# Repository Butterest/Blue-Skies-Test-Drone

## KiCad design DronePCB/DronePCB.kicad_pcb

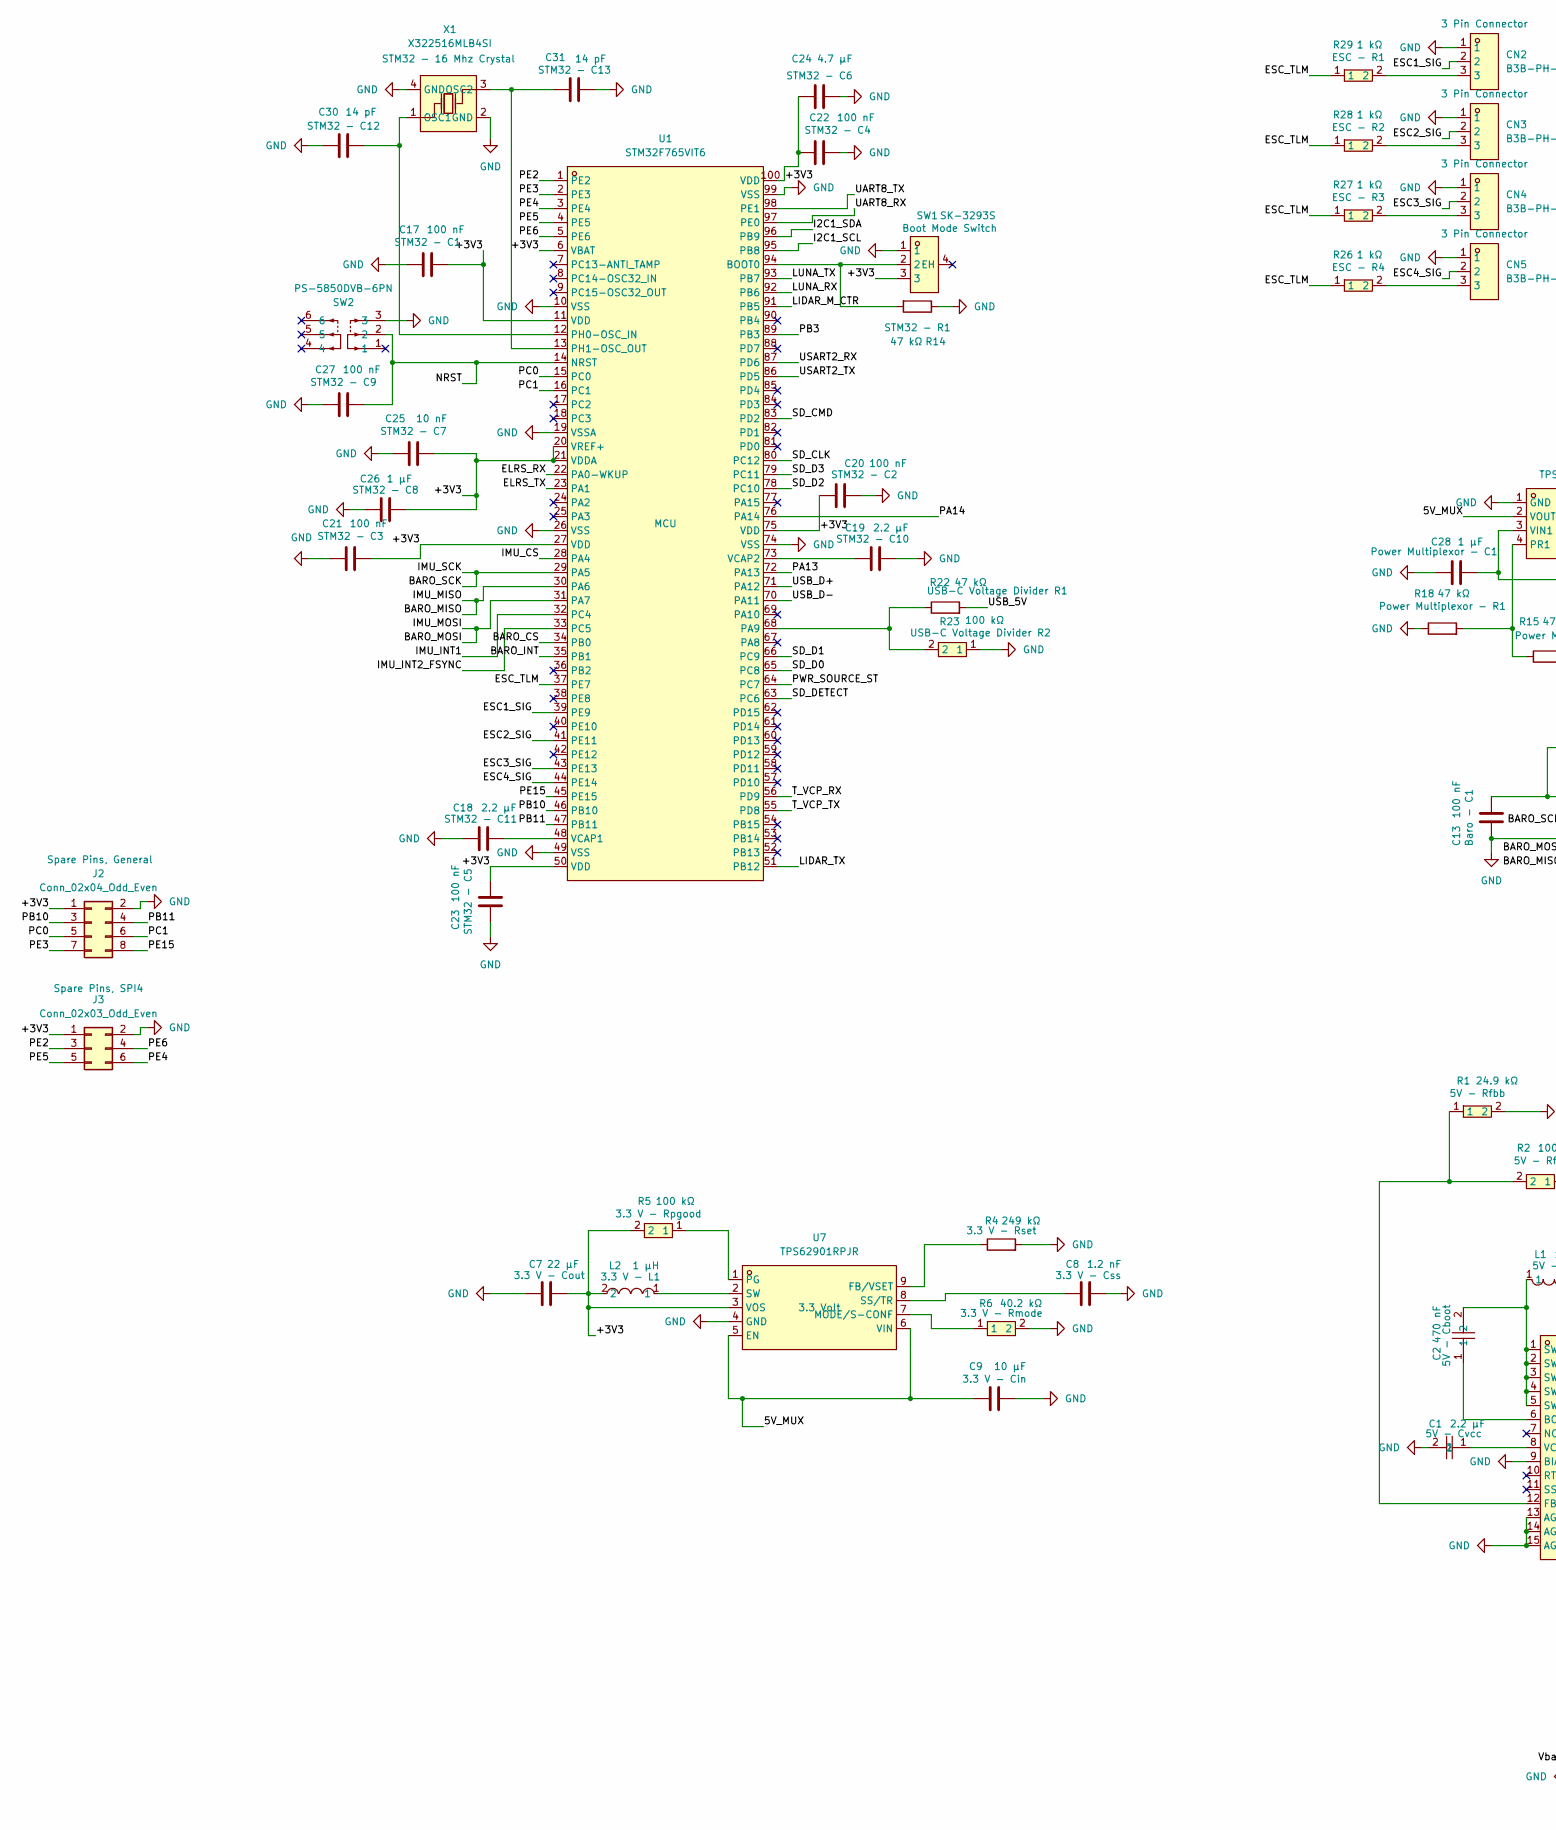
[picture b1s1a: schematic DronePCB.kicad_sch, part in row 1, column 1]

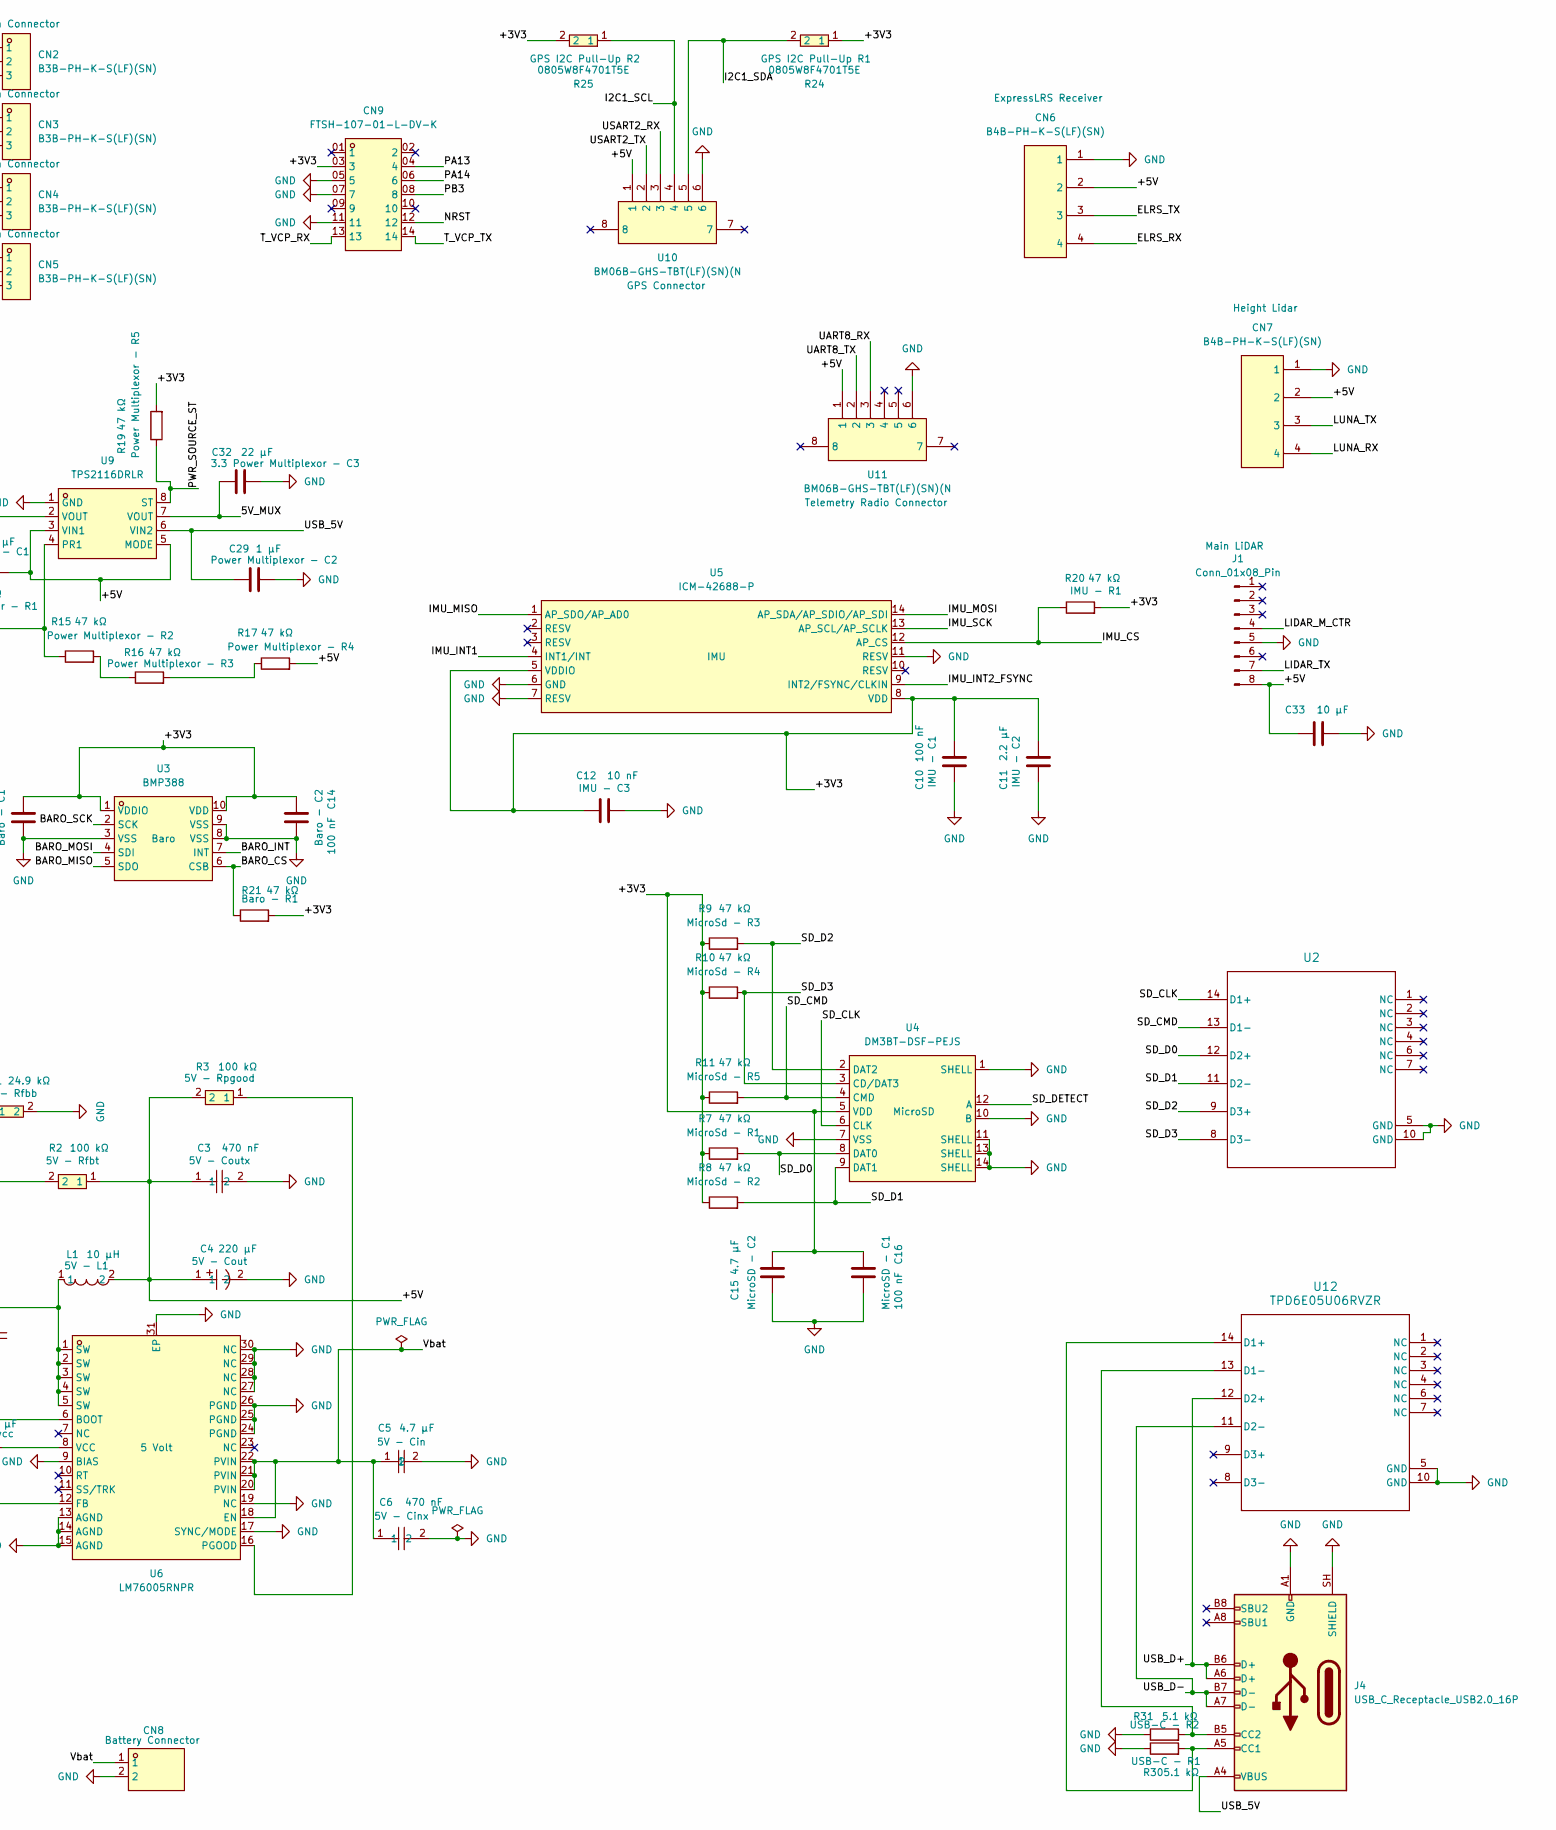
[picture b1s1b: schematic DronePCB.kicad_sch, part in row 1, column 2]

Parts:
C1, C18, C19: 2.2 µF; C_0603_1608Metric; Manufacturer Part # CL10A225KO8NNNC; LCSC Part C23630
C2: 470 nF; C_0402_1005Metric; Manufacturer Part # GRM155R61A474KE15D; LCSC Part C77003
C3: 470 nF; C_0805_2012Metric; Manufacturer Part # EMF212B7474KGHT; LCSC Part C651004
C4: 220 µF; CAP-SMD_L7.3-W4.3; Manufacturer Part # 593D227X0010E2TE3; LCSC Part C1952898
C5, C15, C24: 4.7 µF; C_1206_3216Metric; Manufacturer Part # GRM31CR71H475KA12L; LCSC Part C77096
C6: 470 nF; C_0805_2012Metric; Manufacturer Part # CGA4J3X7R1H474K125AB; LCSC Part C3899838
C7, C32: 22 µF; C_0805_2012Metric; Manufacturer Part # MSASE21GBB5226MTNA01; LCSC Part C140602
C8: 1.2 nF; C_0603_1608Metric; Manufacturer Part # GRM1885C1H122JA01D; LCSC Part C97876
C9, C33: 10 µF; C_0805_2012Metric; Manufacturer Part # MSASE21GAB5106KTNA01; LCSC Part C6684487
C10, C13, C14, C16, C17, C20, C21, C22, C23, C27: 100 nF; C_0402_1005Metric; MPN CL05B104KO5NNNC; LCSC Part C1525
C11: 2.2 µF; C_0805_2012Metric; MPN CL05B104KO5NNNC; LCSC Part C125847
C12, C25: 10 nF; C_0402_1005Metric; MPN CL05B104KO5NNNC; LCSC Part C1524
C26, C28, C29: 1 µF; C_0603_1608Metric; LCSC Part C5199872
C30, C31: 14 pF; C_0402_1005Metric; MPN 0402CG140J500NT; LCSC Part C3037644
CN2, CN3, CN4, CN5: B3B-PH-K-S(LF)(SN); JST_PH_B3B-PH-K_1x03_P2.00mm_Vertical; LCSC Part C131339
CN6, CN7: B4B-PH-K-S(LF)(SN); JST_PH_B4B-PH-K_1x04_P2.00mm_Vertical; LCSC Part C131334
CN8: B2P-VH (LF)(SN); CONN-TH_B2P-VH-LF-SN; MPN B2P-VH (LF)(SN); LCSC Part C160315
CN9: FTSH-107-01-L-DV-K; HDR-SMD_14P-P1.27_FTSH-107-01-L-DV-K; LCSC Part C5307809
J1: Conn_01x08_Pin; JST_PH_B8B-PH-K_1x08_P2.00mm_Vertical; LCSC Part C594302
J2: Conn_02x04_Odd_Even; PinHeader_2x04_P2.54mm_Vertical
J3: Conn_02x03_Odd_Even; PinHeader_2x03_P2.54mm_Vertical
J4: USB_C_Receptacle_USB2.0_16P; USB_C_Receptacle_HRO_TYPE-C-31-M-12; LCSC Part C165948
L1: 10 µH; IND-SMD_L10.2-W10.2-LS10.8; Manufacturer Part # IHLP4040DZER100M01; LCSC Part C845065
L2: 1 µH; L0806; Manufacturer Part # DFE201610E-1R0M=P2; LCSC Part C161082
R1: 24.9 kΩ; R_0603_1608Metric; Manufacturer Part # RC0603FR-0724K9L; LCSC Part C137761
R2, R5, R23: 100 kΩ; R_0402_1005Metric; Manufacturer Part # CRCW0402100KFKED; LCSC Part C481918
R3: 100 kΩ; R_0603_1608Metric; Manufacturer Part # CRCW0603100KFKEA; LCSC Part C844916
R4: 249 kΩ; R_0402_1005Metric; Manufacturer Part Number CRCW0402249KFKEDC; LCSC Part C3009708
R6: 40.2 kΩ; R_0402_1005Metric; Manufacturer Part # CRCW040240K2FKED; LCSC Part C844507
R7, R8, R9, R10, R11, R14, R15, R16, R17, R18, R19, R20, R21, R22: 47 kΩ; R_0805_2012Metric; LCSC Part C17713
R24, R25: 0805W8F4701T5E; R_0805_2012Metric; LCSC Part C17673
R26, R27, R28, R29: 1 kΩ; R_1206_3216Metric; MPN 1206W4J0102T5E; LCSC Part C1469
R30, R31: 5.1 kΩ; R_0805_2012Metric; MPN RESI PTFR0805B5K10P9; LCSC Part C2692693
SW1: SK-3293S; SW-SMD_SK-3293S; LCSC Part C466006
SW2: PS-5850DVB-6PN; SW-TH_6P-L5.8-W5.8-P2.00-LS4.5-BL_1; LCSC Part C5362623
U1: STM32F765VIT6; LQFP-100_L14.0-W14.0-P0.50-LS16.0-BL; LCSC Part C710319
U2, U12: TPD6E05U06RVZR; RVZ0014A; LCSC Part C962978
U3: BMP388; LGA-10_L2.0-W2.0-P0.50-BL; LCSC Part C779278
U4: DM3BT-DSF-PEJS; SIM-SMD_DM3BT-DSF-PEJS; LCSC Part C597972
U5: ICM-42688-P; LGA-14_L3.0-W2.5-P0.50-TL; LCSC Part C1850418
U6: LM76005RNPR; WQFN-30_L6.0-W4.0-P0.50-TL-EP_LM76005RNPR; LCSC Part C2866241
U7: TPS62901RPJR; VQFN-HR-9_L2.0-W1.5-P0.50-BL_TI_RPJ; LCSC Part C2864847
U9: TPS2116DRLR; SOT-583-8_L2.1-W1.6-P0.50-LS1.6-BL; LCSC Part C3235557
U10, U11: BM06B-GHS-TBT(LF)(SN)(N; CONN-SMD_6P-P1.25_BM06B-GHS-TBT-LF-SN-N; LCSC Part C189892
X1: X322516MLB4SI; CRYSTAL-SMD_4P-L3.2-W2.5-BL; LCSC Part C13738

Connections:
/5V_MUX: C9.1, C32.2, U7.5 (EN), U7.6 (VIN), U9.2 (VOUT), U9.7 (VOUT)
/+3V3: C7.1, C10.2, C11.2, C12.1, C13.2, C14.1, C15.2, C16.1, C17.2, C20.1, C21.2, C22.1, C23.2, C24.1, C25.2, C26.2, CN9.03 (3), J2.1, J3.1, L2.2, R5.2, R7.1, R8.1, R9.1, R10.1, R11.1, R19.2, R20.2, R21.2, R24.1, R25.2, SW1.3, U1.6 (VBAT), U1.11 (VDD), U1.20 (VREF+), U1.21 (VDDA), U1.27 (VDD), U1.50 (VDD), U1.75 (VDD), U1.100 (VDD), U3.1 (VDDIO), U3.10 (VDD), U4.5 (VDD), U5.5 (VDDIO), U5.8 (VDD), U7.3 (VOS)
/+5V: C3.1, C4.1, C28.2, C33.1, CN6.2, CN7.2, J1.8, L1.2, R2.1, R3.2, R17.2, U9.3 (VIN1), U9.5 (MODE), U10.1, U11.1
/BARO_CS: R21.1, U1.34 (PB0), U3.6 (CSB)
/BARO_INT: U1.35 (PB1), U3.7 (INT)
/BARO_MISO: U1.30 (PA6), U3.5 (SDO), U5.1 (AP_SDO/AP_AD0)
/BARO_MOSI: U1.31 (PA7), U3.4 (SDI), U5.14 (AP_SDA/AP_SDIO/AP_SDI)
/BARO_SCK: U1.29 (PA5), U3.2 (SCK), U5.13 (AP_SCL/AP_SCLK)
/ELRS_RX: CN6.4, U1.22 (PA0-WKUP)
/ELRS_TX: CN6.3, U1.23 (PA1)
/ESC1_SIG: CN2.2, U1.39 (PE9)
/ESC2_SIG: CN3.2, U1.41 (PE11)
/ESC3_SIG: CN4.2, U1.43 (PE13)
/ESC4_SIG: CN5.2, U1.44 (PE14)
/ESC_TLM: R26.1, R27.1, R28.1, R29.1, U1.37 (PE7)
/I2C1_SCL: R25.1, U1.95 (PB8), U10.4
/I2C1_SDA: R24.2, U1.96 (PB9), U10.5
/IMU_CS: R20.1, U1.28 (PA4), U5.12 (AP_CS)
/IMU_INT1: U1.32 (PC4), U5.4 (INT1/INT)
/IMU_INT2_FSYNC: U1.33 (PC5), U5.9 (INT2/FSYNC/CLKIN)
/LIDAR_M_CTR: J1.4, U1.91 (PB5)
/LIDAR_TX: J1.7, U1.51 (PB12)
/LUNA_RX: CN7.4, U1.92 (PB6)
/LUNA_TX: CN7.3, U1.93 (PB7)
/NRST: C27.2, CN9.12, SW2.2, U1.14 (NRST)
/PA13: CN9.04 (4), U1.72 (PA13)
/PA14: CN9.06 (6), U1.76 (PA14)
/PB3: CN9.08 (8), U1.89 (PB3)
/PB10: J2.3, U1.46 (PB10)
/PB11: J2.4, U1.47 (PB11)
/PC0: J2.5, U1.15 (PC0)
/PC1: J2.6, U1.16 (PC1)
/PE2: J3.3, U1.1 (PE2)
/PE3: J2.7, U1.2 (PE3)
/PE4: J3.6, U1.3 (PE4)
/PE5: J3.5, U1.4 (PE5)
/PE6: J3.4, U1.5 (PE6)
/PE15: J2.8, U1.45 (PE15)
/PWR_SOURCE_ST: R19.1, U1.64 (PC7), U9.8 (ST)
/SD_CLK: U1.80 (PC12), U2.14 (D1+), U4.6 (CLK)
/SD_CMD: R11.2, U1.83 (PD2), U2.13 (D1-), U4.4 (CMD)
/SD_D0: R7.2, U1.65 (PC8), U2.12 (D2+), U4.8 (DAT0)
/SD_D1: R8.2, U1.66 (PC9), U2.11 (D2-), U4.9 (DAT1)
/SD_D2: R9.2, U1.78 (PC10), U2.9 (D3+), U4.2 (DAT2)
/SD_D3: R10.2, U1.79 (PC11), U2.8 (D3-), U4.3 (CD/DAT3)
/SD_DETECT: U1.63 (PC6), U4.12 (A)
/T_VCP_RX: CN9.13, U1.56 (PD9)
/T_VCP_TX: CN9.14, U1.55 (PD8)
/UART8_RX: U1.97 (PE0), U11.3
/UART8_TX: U1.98 (PE1), U11.2
/USART2_RX: U1.87 (PD6), U10.3
/USART2_TX: U1.86 (PD5), U10.2
/USB_5V: C29.1, J4.A4 (VBUS), J4.A9 (VBUS), J4.B4 (VBUS), J4.B9 (VBUS), R22.2, U9.6 (VIN2)
/USB_D+: J4.A6 (D+), J4.B6 (D+), U1.71 (PA12), U12.12 (D2+)
/USB_D-: J4.A7 (D-), J4.B7 (D-), U1.70 (PA11), U12.11 (D2-)
/Vbat: C5.1, C6.1, CN8.1, U6.18 (EN), U6.20 (PVIN), U6.21 (PVIN), U6.22 (PVIN)
GND: C1.2, C3.2, C4.2, C5.2, C6.2, C7.2, C8.2, C9.2, C10.1, C11.1, C12.2, C13.1, C14.2, C15.1, C16.2, C17.1, C18.1, C19.2, C20.2, C21.1, C22.2, C23.1, C24.2, C25.1, C26.1, C27.1, C28.1, C29.2, C30.1, C31.2, C32.1, C33.2, CN2.1, CN3.1, CN4.1, CN5.1, CN6.1, CN7.1, CN8.2, CN9.05 (5), CN9.07 (7), CN9.11, J1.5, J2.2, J3.2, J4.A1 (GND), J4.A12 (GND), J4.B1 (GND), J4.B12 (GND), J4.SH (SHIELD), R1.2, R4.2, R6.2, R14.1, R18.1, R23.1, R30.1, R31.1, SW1.1, SW2.3, U1.10 (VSS), U1.19 (VSSA), U1.26 (VSS), U1.49 (VSS), U1.74 (VSS), U1.99 (VSS), U2.5 (GND), U2.10 (GND), U3.3 (VSS), U3.8 (VSS), U3.9 (VSS), U4.1 (SHELL), U4.7 (VSS), U4.10 (B), U4.11 (SHELL), U4.13 (SHELL), U4.14 (SHELL), U5.6 (GND), U5.7 (RESV), U5.11 (RESV), U6.9 (BIAS), U6.13 (AGND), U6.14 (AGND), U6.15 (AGND), U6.17 (SYNC/MODE), U6.19 (NC), U6.24 (PGND), U6.25 (PGND), U6.26 (PGND), U6.27 (NC), U6.28 (NC), U6.29 (NC), U6.30 (NC), U6.31 (EP), U7.4 (GND), U9.1 (GND), U10.6, U11.6, U12.5 (GND), U12.10 (GND), X1.2 (GND), X1.4 (GND)
unnamed: C2.2, L1.1, U6.1 (SW), U6.2 (SW), U6.3 (SW), U6.4 (SW), U6.5 (SW)
unnamed: CN2.3, R29.2
unnamed: CN3.3, R28.2
unnamed: CN4.3, R27.2
unnamed: CN5.3, R26.2
unnamed: J4.A5 (CC1), R30.2, U12.14 (D1+)
unnamed: J4.B5 (CC2), R31.2, U12.13 (D1-)
unnamed: R15.2, R16.1
unnamed: R16.2, R17.1
unnamed: R14.2, SW1.2, U1.94 (BOOT0)
unnamed: R22.1, R23.2, U1.68 (PA9)
unnamed: C30.2, U1.12 (PH0-OSC_IN), X1.1 (OSC1)
unnamed: C31.1, U1.13 (PH1-OSC_OUT), X1.3 (OSC2)
unnamed: C18.2, U1.48 (VCAP1)
unnamed: C19.1, U1.73 (VCAP2)
unnamed: C2.1, U6.6 (BOOT)
unnamed: R1.1, R2.2, U6.12 (FB)
unnamed: R3.1, U6.16 (PGOOD)
unnamed: C1.1, U6.8 (VCC)
unnamed: R4.1, U7.9 (FB/VSET)
unnamed: R6.1, U7.7 (MODE/S-CONF)
unnamed: R5.1, U7.1 (PG)
unnamed: C8.1, U7.8 (SS/TR)
unnamed: L2.1, U7.2 (SW)
unnamed: R15.1, R18.2, U9.4 (PR1)

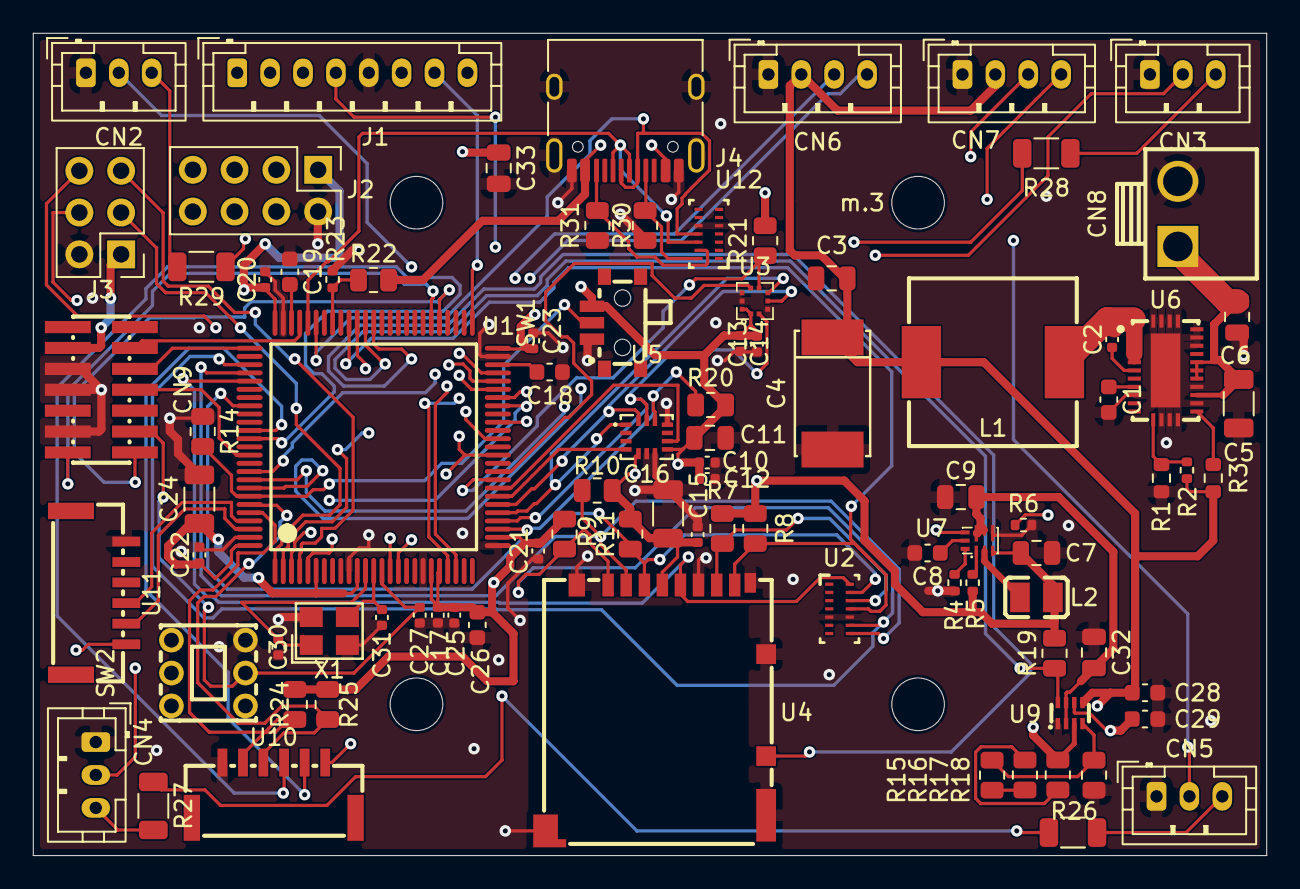
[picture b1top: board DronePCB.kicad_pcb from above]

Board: 4 copper layers, 75.0 x 50.0 mm, 91 parts (0 on the bottom side), 82 nets.

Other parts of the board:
m.3: MountingHole_3.2mm_M3
